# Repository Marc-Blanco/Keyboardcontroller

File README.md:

# Keyboardcontroller 
It´s a keyboard with the objective of being a leverless controller inspired by the arcade controllers specially designed for playing fgc games. All controlled with a raspberrypi PICO. It's main prupose its to serve as a controller for Street fighter, Tekken, etc... But it's sure that I will find more uses to it. It's Inspired by [Hitbox controllers](https://www.hitboxarcade.com/) and I do plan on making a levered version of it, it could be interpreted as a Keyboard extension also.

## PCB
Schematic

PCB

## CAD
All fitted togheter

## Assembly

# Firmware
I found already done Firmware for raspberrypi picos https://github.com/OpenStickCommunity/GP2040-CE?tab=readme-ov-file

## BOM
| Part                                 | Quantity | Price  | Link                                                                                                                                                                                                                                                                                                                                                                                                                                                                                          | Notes                                                      |
| ------------------------------------ | -------- | ------ | --------------------------------------------------------------------------------------------------------------------------------------------------------------------------------------------------------------------------------------------------------------------------------------------------------------------------------------------------------------------------------------------------------------------------------------------------------------------------------------------- | ---------------------------------------------------------- |
| PCB                          | 5        | $25.86 + 25$ for customs | [JLCPCB](https://jlcpcb.com/)                                                                                                                                                                                | Yes, the shipment charges cost 25$. All this include the PCB the top case the bottom part and the buttons                                                                                                                                                                                                                                                                              |                             |
| Kailh Low Profile Choc Switches    | 14        | €26.35 | [splitkb](https://splitkb.com/products/kailh-low-profile-choc-switches)                                                                                                                                                                                                                                                                                                                                                                                                                                       | Dutch company avoiding potential customs                        |
| Raspberrypi Pico                 | 1       | $0.99  | [Aliexpress](https://es.aliexpress.com/item/1005003371056277.html?spm=a2g0o.productlist.main.1.64b0TBujTBujqQ&algo_pvid=f291c49f-37b8-4414-9bc8-1c92e40f57c4&pdp_ext_f=%7B%22order%22%3A%222296%22%2C%22eval%22%3A%221%22%7D&utparam-url=scene%3Asearch%7Cquery_from%3A)                                                                                                                                                          | Aliexpress Quality     
 | Total cost | | 80,57,7 |                                                                                                                                                                                                                                                 

---

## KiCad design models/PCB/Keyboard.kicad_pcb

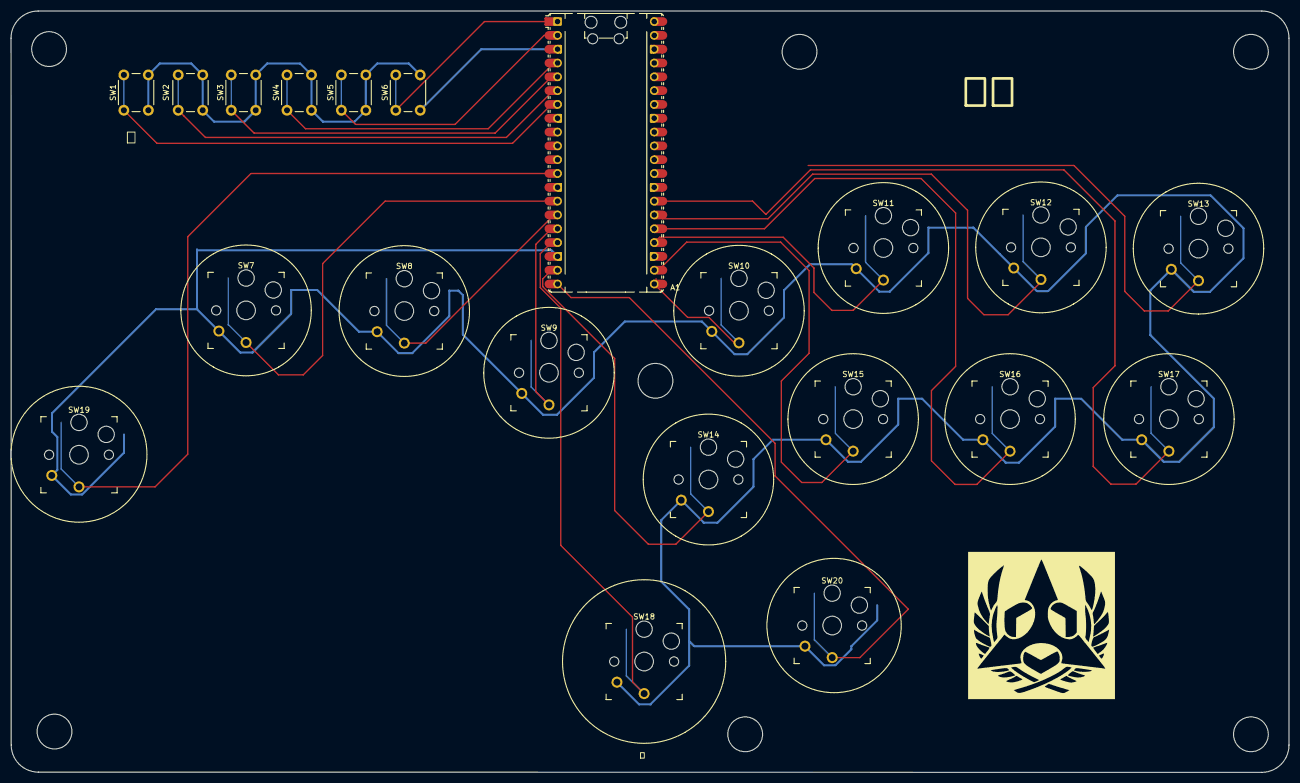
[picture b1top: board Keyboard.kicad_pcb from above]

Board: 2 copper layers, 235.0 x 140.0 mm, 21 parts (0 on the bottom side), 21 nets.

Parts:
A1: RaspberryPi_Pico; RaspberryPi_Pico_Common_Unspecified
SW1, SW2, SW3, SW4, SW5, SW6: SW_Push; SW_PUSH_6mm_H5mm
SW7, SW8, SW9, SW10, SW11, SW12, SW13, SW14, SW15, SW16, SW17, SW18, SW19, SW20: SW_Push; Kailh_socket_PG1350_optional

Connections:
CIRCLE: A1.22 (GPIO17), SW15.1
CROSS: A1.19 (GPIO14), SW14.1
DOWN: A1.15 (GPIO11), SW8.1
GND: A1.3 (GND), A1.8 (GND), A1.13 (GND), A1.18 (GND), A1.23 (GND), A1.28 (GND), A1.38 (GND), SW1.2, SW2.2, SW3.2, SW4.2, SW5.2, SW6.2, SW7.2, SW8.2, SW9.2, SW10.2, SW11.2, SW12.2, SW13.2, SW14.2, SW15.2, SW16.2, SW17.2, SW18.2, SW19.2, SW20.2
L1: A1.29 (GPIO22), SW13.1
L2: A1.27 (GPIO21), SW17.1
L3: A1.20 (GPIO15), SW20.1
LEFT: A1.14 (GPIO10), SW7.1
OPT1: A1.7 (GPIO5), SW1.1
OPT2: A1.6 (GPIO4), SW2.1
OPT3: A1.5 (GPIO3), SW3.1
OPT4: A1.4 (GPIO2), SW4.1
OPT5: A1.2 (GPIO1), SW5.1
OPT6: A1.1 (GPIO0), SW6.1
R1: A1.26 (GPIO20), SW12.1
R2: A1.25 (GPIO19), SW16.1
R3: A1.12 (GPIO9), SW19.1
RIGHT: A1.16 (GPIO12), SW9.1
SQUARE: A1.21 (GPIO16), SW10.1
TRIANGLE: A1.24 (GPIO18), SW11.1
UP: A1.17 (GPIO13), SW18.1

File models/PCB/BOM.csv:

"Id";"Identificador";"Huella";"Cantidad";"Identificación";"Suministrador y ref";
1;"SW8,SW9,SW18,SW10,SW11,SW12,SW13,SW14,SW15,SW16,SW17,SW7,SW20,SW19";"Kailh_socket_PG1350_optional";14;"SW_Push";;;
2;"SW4,SW2,SW5,SW1,SW3,SW6";"SW_PUSH_6mm_H5mm";6;"SW_Push";;;
3;"A1";"RaspberryPi_Pico_Common_Unspecified";1;"RaspberryPi_Pico";;;

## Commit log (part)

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2025-06-30 Create a
2025-07-08 Create e
2025-07-09 Rename models/Sin nombre1.FCStd to models/CAD/Sin nombre1.FCStd
2025-07-09 Rename models/Unnamed1-Body.step to models/CAD/Unnamed1-Body.step
2025-07-09 Rename models/back-Body.step to models/CAD/back-Body.step
2025-08-11 Rename Unnamed1-Body.step to Front.step
2026-01-01 Fix formatting and update cost details in README
2026-01-01 Create PCB
2026-01-01 Add new PCBa model
